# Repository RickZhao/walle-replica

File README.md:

# Wall-E Robot Replica
Robot and controller code for a Wall-E replica robot. For more information about the robot, visit https://wired.chillibasket.com/3d-printed-archive/arduino-pi/wall-e/

<br />

> **This fork adds two extra firmwares and custom hardware on top of the upstream project:**
>
> | Path | Framework | Description |
> |------|-----------|-------------|
> | `wall-e_xiaozhi/` | ESP-IDF | **Mainline**: single ESP32-S3 voice robot based on xiaozhi-esp32 (wake word + cloud LLM + MCP motion tools + web control panel + ML307R-DL 4G fallback (mini core board, GPIO2/3); eye display lives on the CAM module, disabled on the main MCU). See `docs/XIAOZHI_MIGRATION.md` |
> | `wall-e_esp32_cam/` | Arduino (ESP32-S3-CAM) | MJPEG camera streamer for a second ESP32-S3-CAM board |
> | `hardware/walle-shield/` | KiCad 10 | Modular backplane PCB replacing dupont wiring |
> | `hardware/` | — | New-hardware PCB design inputs: `另一套硬件方案.md` (third-party kit BOM), `新硬件BOM与尺寸.md` (BOM/sizes), `主板设计说明.md` (connectors/power/layout), `主板布局示意图.html` (layout incl. camera backplane & panel board) |
>
> The original Arduino UNO (`archive/arduino-pi/wall-e/`) + Raspberry Pi (`archive/arduino-pi/web_interface/`) setup below is still fully maintained. Chinese docs live in `docs/` (serial protocol, wiring, hardware list, migration notes).

<br />
<br />

## 1. Arduino Code (wall-e)
Main program to control the motors and servos of the robot. Features include:
1. An animation queue, keeping track of the next servo movements the robot needs to perform.
1. A random movement generator, allowing the robot to autonomously move and appear animated.
1. Velocity control of all servo motors, facilitating smooth accelerations and decelerations. 
1. Non-blocking serial parsing, allowing the movements of the robot to be remote controlled.
1. Battery level monitoring using a potential divider circuit.
<br />

## 2. Raspberry Pi Web Server (web_interface)
The web interface is programmed in Python and uses *Flask* to generate a server. The Raspberry Pi is connected via USB to the Arduino micro-controller. The main features are:
1. A JavaScript joystick, with which the movement of the robot can easily be controller.
1. Manual control of all the servo motors.
1. A list of movement animations which can be performed by the robot.
1. A list of sounds which can be played.
1. Settings page, where motor parameters, sound volume, and video options can be modified.
1. Gamepad support; on any modern browsers, you can use a connected Xbox of PlayStation controller to control the robot.
1. A simple login page to prevent everyone from having access to the controls (note: this is not a full access control system, please don't use this web interface on untrusted/public networks)
1. **[New]** Support for text-to-speech
1. **[New]** Program robot actions using CodeBlocks drag and drop editor within the browser.

*Image of the web interface and robot*

<br />
<br />

## Setup Instructions

### 1. Arduino

#### [a] Basic Installation
1. Ensure that the wiring of the electronics matches the diagram shown below.
1. Download/clone the folder "wall-e" from the GitHub repository.
1. Open `wall-e.ino` in the Arduino IDE; the files `animations.ino`, `MotorController.hpp` and `Queue.hpp` should automatically open on separate tabs of the IDE as well.
1. Install the `Adafruit_PWMServoDriver.h` library
	1. Go to Sketch -> Include Library -> Manage Libraries...
	1. Search for *Adafruit Servo*.
	1. Install latest version of the library.
1. Connect to the computer to the micro-controller with a USB cable. Ensure that the correct *Board* and *Port* are selected in the *Tools* menu.
1. Upload the sketch to the micro-controller.

*Diagram showing the wiring of the robot's electronic components*
<br />

> **New: Modular Backplane PCB** — A complete KiCad 10 backplane design is available in `hardware/walle-shield/`. It replaces the mess of dupont wires with a single 140×100 mm 2-layer board: solder the pin sockets/terminals/switch/fuse/resistors, then plug in the Arduino, TB6612FNG module, PCA9685 module and buck converter. Gerbers, drill files and BOM are already exported. See `hardware/walle-shield/README.md` for details.

> **New: New-hardware PCB design inputs (Plan A)** — Complete design inputs for the custom Plan-A double-sided stacked mainboard + camera backplane + front-panel board are ready in `hardware/`: `新硬件BOM与尺寸.md` (BOM & measured module sizes), `主板设计说明.md` (pin-by-pin connector definitions / power tree / layout), `主板布局示意图.html` (to-scale layout incl. mainboard top/bottom, camera backplane and panel board); referencing the third-party kit (`另一套硬件方案.md` + `另一套硬件-{主板,副板,摄像头背板}.png`).
<br />

<br />

#### [b] Testing the Main Program
1. Once the sketch has been uploaded to the Arduino, power on the 12V battery while the micro-controller is still connected to the computer.
1. Open the *Serial Monitor* (button in top-right of Arduino IDE). Set the baud rate to 115200.
1. To control the movement of the robot, send the characters 'w', 'a', 's' or 'd' to move forward, left, back or right respectively. Send 'q' to stop all movement.
1. To move the head, send the characters 'j', 'l', 'i' or 'k' to tilt the head left or right and the eyes upwards or downwards. At this stage, the servos may try to move further than they should and may look uncoordinated. This will be solved by performing the servo motor calibration steps below.

<br />

#### [c] Servo Motor Calibration
1. Download/clone the folder "wall-e_calibration" from the GitHub repository
1. Open `wall-e_calibration.ino` in the Arduino IDE.
1. Upload the sketch to the micro-controller, and open the serial monitor and set the baud rate to 115200.
1. The sketch is used to calibrate the maximum and minimum PWM pulse lengths required to move each servo motor across its desired range of motion. The standard LOW and HIGH positions of each of the servos can be seen on diagrams [on my website](https://wired.chillibasket.com/3d-printed-archive/arduino-pi/wall-e/). 
1. When starting the sketch and opening the serial monitor, a message should appear after 2-3 seconds, saying that it is ready to calibrate the LOW position of the first servo motor (the head rotation).
1. Send the character 'a' and 'd' to move the motor backwards and forwards by -10 and +10. For finer control, use the characters 'z' and 'c' to move the motor by -1 and +1. 
1. Once the motor is in the correct position, send the character 'n' to proceed to the calibration step. It will move on to the HIGH position of the same servo, after which the process will repeat for each of the 7 servos in the robot.
1. When all joints are calibrated, the sketch will output an array containing the calibration values to the serial monitor.
1. Copy the array, and paste it into [lines 144](https://github.com/chillibasket/walle-replica/blob/master/archive/arduino-pi/wall-e/wall-e.ino#L144) to 150 of the program *wall-e.ino*. The array should look similar to this:
    ```cpp
    int preset[][2] =  {{410,120},  // head rotation
                        {532,178},  // neck top
                        {120,310},  // neck bottom
                        {465,271},  // eye right
                        {278,479},  // eye left
                        {340,135},  // arm left
                        {150,360}}; // arm right
    ```

<br />

#### [d] Battery Level Detection (Optional)
When using batteries to power the robot, it is important to keep track of how much power is left. Some batteries may break if they are over-discharged, and the SD card of the Raspberry Pi may become corrupted if not enough power is delivered.
1. To use the battery level detection feature on the Arduino, connect the following resistors and wiring as shown in the image below. The resistors (potential divider) reduce the 12V voltage down to a value below 5V, which is safe for the Arduino to measure using its analogue pins. The recommended resistor values are `R1 = 100kΩ` and `R2 = 47kΩ`.
1. Uncomment [line 54](https://github.com/chillibasket/walle-replica/blob/master/archive/arduino-pi/wall-e/wall-e.ino#L54) `#define BAT_L` in the main Arduino sketch *wall-e.ino*.
1. If you are using different resistor values, change the value of the potential divider gain factor on line 54 of the sketch, according to the formula: `POT_DIV = R2 / (R1 + R2)`. 
1. The program should now automatically check the battery level every 10 seconds, and this level will be shown on the Raspberry Pi web-interface in the "Status" section.

<br />
*Diagram showing the wiring of the battery level detection circuit*

<br />

#### [e] oLed Display (Optional) (Contributed by: [hpkevertje](https://github.com/hpkevertje))
It is possible to integrate a small oLED display which will show the battery level of the robot on the front battery indicator panel. This feature requires the battery level detection circuit in the previous section to be enabled, and the screen will update every time the battery level is calculated. This function uses the u8g2 display library in page mode; on the Arduino UNO you may get a warning that the memory usage is high, but this warning can be ignored. 
1. To use the oLed display feature on the Arduino, connect an i2c oLed display to the i2c bus on the servo motor module (see diagram).
1. Install the U8g2 library in the Arduino library manager:
    1. Go to Sketch -> Include Library -> Manage Libraries...
    1. Search for *U8gt*. The library publisher is "oliver".
    1. Install the latest version of the library.
1. Uncomment [line 74](https://github.com/chillibasket/walle-replica/blob/master/archive/arduino-pi/wall-e/wall-e.ino#L74) `#define OLED` in the main Arduino sketch *wall-e.ino*.
1. If you are using a different display that is supported by the library, you can change the constructor on [line 78](https://github.com/chillibasket/walle-replica/blob/master/archive/arduino-pi/wall-e/wall-e.ino#L78) as documented on the [library reference page](https://github.com/olikraus/u8g2/wiki/u8g2setupcpp#constructor-reference). The default is for an SH1106_128X64_NONAME display.

<br />
*Diagram showing the wiring of the oLed display*

<br />

#### [f] Adding your own Servo Animations (Optional)
My code comes with two animations which replicate scenes from the movie; the eye movement Wall-E does when booting-up, and a sequence of motions as Wall-E inquisitively looks around. From version 2.7 of the code, I've now made it easier to add your own servo motor animations so that you can make your Wall-E do other movements...
1. Open up the file `animations.ino`, which is located in the same folder as the main Arduino sketch. 
1. Each animation command consists of the positions you want all the servo motors to move to, and the amount of time the animation should wait until moving on to the next instruction.
1. You can add a new animation by inserting an extra `case` section into the switch statement. You should slot your extra code into the space above the `default` section. For example:
    ```cpp
    case 3:
            // --- Title of your new motion sequence ---
            //          time,head,necT,necB,eyeR,eyeL,armL,armR
            queue.push({  12,  48,  40,   0,  35,  45,  60,  59});
            queue.push({1500,  48,  40,  20, 100,   0,  80,  80});
            // Add as many additional movements here as you need to complete the animation
            // queue.push({time, head rotation, neck top, neck bottom, eye right, eye left, arm left, arm right})
            break;
    ```
1. The time needs to be a number in milliseconds (for example, 3.5 seconds = 3500)
1. The servo motor position commands need to be an integer number between 0 to 100, where `0 = LOW` and `100 = HIGH` servo position as calibrated in the `wall-e_calibration.ino` sketch.
1. If you want to disable a motor for a specific move, you can use -1. 

<br />
<br />

### 2. Raspberry Pi Web Server

#### [a] Hardware Setup
1. Connect the power cable of the Raspberry Pi to the USB power output port on the 12V to 5V buck converter.
2. Connect the USB data cable from the Arduino to the Raspberry Pi.
3. If you have a Raspberry Pi camera, plug the ribbon cable into the CSI camera connector.
4. For setup and installation, you can plug in a monitor into the HDMI port and a USB keyboard and mouse. Alternatively you can connect to and configure the Raspberry Pi from a different computer [using SSH](https://www.raspberrypi.com/documentation/computers/remote-access.html#ssh).
 
<br />

#### [b] Basic Installation
1. Setup the Raspberry Pi to run the latest version of Raspberry Pi OS Desktop. The setup instructions can be found on the [Raspberry Pi website](https://www.raspberrypi.com/documentation/computers/getting-started.html). Make sure that the Raspberry Pi is connected to the internet. 
2. Open the "Terminal" command line on the Raspberry Pi.
3. Clone repository into the home directory of the Raspberry Pi:
```shell
cd ~
git clone https://github.com/chillibasket/walle-replica.git
```

<br />

> [!NOTE]
> You can configure the web-interface settings by editing the "config.py" file:
> * Open the config file: `nano ~/walle-replica/archive/arduino-pi/web_interface/config.py`
> * On line [14](https://github.com/chillibasket/walle-replica/blob/master/archive/arduino-pi/web_interface/config.py#L14) you can change the password for the web interface. The default password is "walle"
> * On line [15](https://github.com/chillibasket/walle-replica/blob/master/archive/arduino-pi/web_interface/config.py#L15) the default serial port which is used to connect to the Arduino can be set. You can find a list of all the connected serial ports using the `dmseg | grep tty` command.
> * On lines [16](https://github.com/chillibasket/walle-replica/blob/master/archive/arduino-pi/web_interface/config.py#L16) and [17](https://github.com/chillibasket/walle-replica/blob/master/archive/arduino-pi/web_interface/config.py#L17) you can configure whether the Arduino and camera should automatically connect when starting up the web server.

<br />

4. Once you have finished editing the configurations, run the installation script which sets up all the required libraries for you (note - this may take some time to complete):
```shell
cd ~/walle-replica
sudo chmod +x ./archive/arduino-pi/raspi-setup.sh
sudo ./archive/arduino-pi/raspi-setup.sh
```

<br />

#### [c] Using the Web Server
1. If the installation completed successfully, the webserver should start automatically when the Raspberry Pi is powered on. This is done using a [Systemd service](https://learn.sparkfun.com/tutorials/how-to-run-a-raspberry-pi-program-on-startup/all#method-3-systemd). 
1. On the Raspberry Pi you can view the web interface from the browser at http://localhost:5000
1. To view the interface from a different computer on the same WiFi network, you first need to determine the current IP address of the Raspberry Pi on your network using the command: `hostname -I`
1. To access the web interface, open a browser on any computer/device on the same network and type in the IP address of the Raspberry Pi, follow by `:5000`. For example `192.168.1.10:5000`
1. To start controlling the robot, you first need to make sure that the serial communication with the Arduino has started. To do this, go to the `Settings` tab of the web-interface, select the correct serial port from the drop-down list and press on the `Reconnect` button. If the configurations were set up correctly, this should happen automatically.

<br />

> [!TIP]
> Here are some useful commands to control the web interface:
> * To stop the automatic web interface service: `sudo systemd stop walle.service`
> * To disable start on boot: `sudo systemd disable walle.service`
> * To reenable start on boot: `sudo systemd enable walle.service`
> * To start the service after it has been stopped: `sudo systemd start walle.service`
> * View the status of the service and check for errors: `sudo systemd status walle.service`
> * If you want to manually run the web server from the terminal, for example to check for errors: `python3 ~/walle-replica/archive/arduino-pi/web_interface/app.py`. You can then press `CTRL + C` to stop the web server again.

<br />

#### [d] Controlling the Robot using Blocky (Contributed by: [dkrey](https://github.com/dkrey))
Since version 3.0, a new tab has been added to the web interface where the robot can be controlled using a drag-and-drop scripting language. Simply drag the actions you want to perform from the left sidebar and drop them into the editor area. For example you can drive Wall-E, move the actuators, and play audio sounds. This is a great way for kids to learn the basics of programming while having fun!

For the commands which drive the motors, you may need to tune the parameters at the bottom of the "config.py" file on lines [25](https://github.com/chillibasket/walle-replica/blob/master/archive/arduino-pi/web_interface/config.py#L25) to [28](https://github.com/chillibasket/walle-replica/blob/master/archive/arduino-pi/web_interface/config.py#L28) to make sure that the speed and turning amount is correct. 

<br />

#### [e] Adding a Camera Stream (Optional)

The web server automatically supports any camera which connects to the CSI connector on the Raspberry Pi with a ribbon cable. Unfortunately USB web cameras are not supported by this system, but I hope to add support for them again in the future. 

<br />

#### [f] Adding new Sounds (Optional)
1. By default the Raspberry should automatically select whether to output audio to the HDMI port or the headphone jack. However, you can ensure that it always uses the headphone jack with the following command: `amixer cset numid=3 1`
1. Make sure that all the sound files you want to use are of type `*.wav`. Most music/sound editors should be able to convert the sound file to this format.
1. Change the file name so that it has the following format: `[group name]_[file name]_[length in milliseconds].wav`. For example: `voice_eva_1200.wav`. In the web-interface, the audio files will be grouped using the "group name" and sorted alphabetically.
1. Upload the sound file to Raspberry Pi in the following folder: `~/walle-replica/archive/arduino-pi/web_interface/static/sounds/`
1. All the files should appear in the web interface when you reload the page. If the files do not appear, you may need to change the privileges required to access the folder: `sudo chmod -R 755 ~/walle-replica/archive/arduino-pi/web_interface/static/sounds`

<br />

#### [g] Set up the Raspberry Pi as a WiFi hotspot *(Optional)*
If you would like to control the robot outdoors or at conventions, there may not be any safe WiFi networks you can connect to. To overcome this issue the Raspberry Pi can broadcast its own WiFi network. You can then connect the computer/phone/tablet you are using to control the robot directly to this network.

To set up the WiFi hotspot, we will use the [RaspAP project](https://raspap.com/) which takes care of all the configuration and tools to get the system working. The following instructions are based on their quick installation guide:

1. Update Raspian, the kernel and firmware (and then reboot):
    ```
    sudo apt-get update
    sudo apt-get dist-upgrade
    sudo reboot now
    ```
1. Ensure that you have set the correct WiFi country in raspi-config’s Localisation Options: `sudo raspi-config`
1. Run the quick installer: `curl -sL https://install.raspap.com | bash`
    1. For the first few yes/no prompts which will appear during the install, type “y” (yes) to accept all of the recommended settings. The final two prompts (Ad Blocking and the next one) are not required so you can type “n” (no) for those.
1. Reboot the Raspberry Pi again to implement the changes: `sudo reboot`
1. Now the Raspberry Pi should be broadcasting a WiFi network with the following details:
    1. SSID (wifi name): `raspi-webgui`
    1. Password: `ChangeMe`
1. After connecting to the WiFi network from a your computer, phone or tablet, the Wall-E web-interface can be opened by typing this address into your browser: `http://10.3.141.1:5000`
1. (Recommended) To change the WiFi name and password, go to the WiFi configuration webpage at: `http://10.3.141.1`. The default username is `admin` and password is `secret`.
    1. Click on “Hotspot” in the left sidebar. In the “Basic” tab you can change the WiFi network name, while the WiFi password can be changed in the “Security” tab.
    1. To change the admin password for the interface used to manage the WiFi settings, click on the “Admin” icon in the top-right of the interface.

<br />
<br />

## Changelog

#### 9th June 2024 (Version 3.0)
1. Major revision of the Python code to implement best practices and make it more robust.
1. Added text to speech and integrated blocky scripting into the web interface (thanks to [dkrey](https://github.com/dkrey) for contributing this).
1. Switched the camera streamer to PiCamera2 since the old streamer no longer worked. 
1. Implemented an installation script to make setup a lot faster and easier. 

#### 31st October 2021 (Version 2.92)
1. Added options in *app.py* to automatically connect to the Arduino and to start the camera stream when the web-interface is opened for the first time.

#### 30th October 2021 (Version 2.91)
1. Changed camera stream port from 8081 to 8080 inline with changes made to the start/stop script.
1. Improved the camera setup instructions, listing all steps explicitly rather than linking to an external repository.

#### 29th May 2021 (Version 2.9)
1. Improved code commenting and variable/parameter naming to make it easier to understand.
1. Fixed bugs related to motor deadzone and trim parameters.

#### 21st March 2021 (Version 2.8)
1. Updated instructions of how to use an oLed display. 

#### 19th December 2020
1. Updated instructions of how to set up a WiFi hotspot on the Raspberry Pi. 
1. Added offline Lato font files to prevent errors when running the web-interface while disconnected from the internet.

#### 7th August 2020 (Version 2.7)
1. Added a soft servo start function to the main Wall-E sketch and the servo calibration sketch. This prevents the servos from jumping as violently on startup.
1. Changed the data-type of the animation queue to reduce the amount of dynamic memory required. Also updated the Queue class so that the buffer memory can be declared globally; this means the compiler can keep track of how much memory the queue actually uses.
1. Moved the preset servo animations into a separate file, to make it easier to add your own animations. 

#### 20th June 2020
1. Minor bug fixes of the `Queue.hpp` and `MotoController.hpp` classes.
1. Updated commenting of code to make it more consistent.

#### 16th February 2020
1. Added gamepad support; any controller can now be used (such as the Xbox or PlayStation controllers) to puppet the robot.
1. Improved serial port handling; in the settings tab, all of the available serial ports are listed in a drop-down menu. 
1. New status indicators are now shown below the video stream. They visualise whether the Arduino and/or gamepad are connected.
1. Added support for battery level detection in both the Arduino code and the Raspberry Pi web interface.
1. Fixed the bug where the virtual joystick no longer worked properly when the window was resized.
1. Plus many other bug fixes!

#### 25th January 2020
1. Restructured the web-interface to make it display more nicely on mobile devices; fancy icons are now used!
1. Added manual servo control - this allows individual servos to be controlled directly from the web-interface.
1. Improved error handling - error messages are now consistently displayed in a pop-up at the bottom of the page.
1. Added instructions about how to automatically start server on boot to the Readme.

#### 31st October 2019
1. Fixed some bugs related to sound playback.
1. Added 2 sample sound files, which ensures that the sound directory is included in the git files.

#### 30th October 2019 
1. Added *wall-e_calibration.ino*, with which the maximum and minimum pulse widths of the servo motors can be calibrated.
1. Updated *wall-e.ino* to use relative coordinates rather than absolute servo pulse widths for the animation presets. This allows the servo calibration data to be used to ensure the movements are the same on all variants of the robot.

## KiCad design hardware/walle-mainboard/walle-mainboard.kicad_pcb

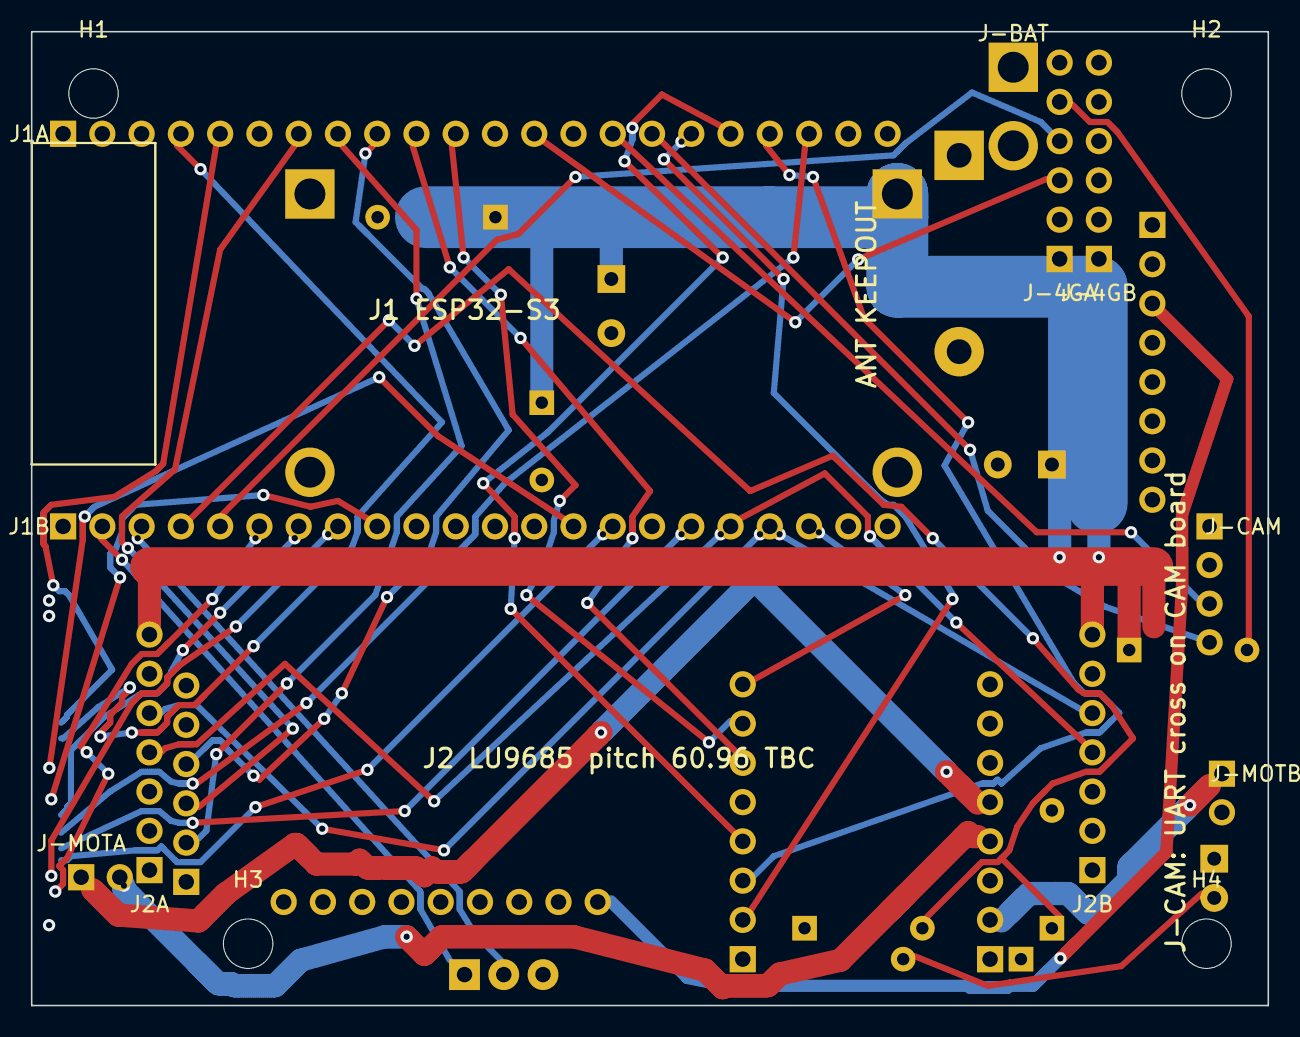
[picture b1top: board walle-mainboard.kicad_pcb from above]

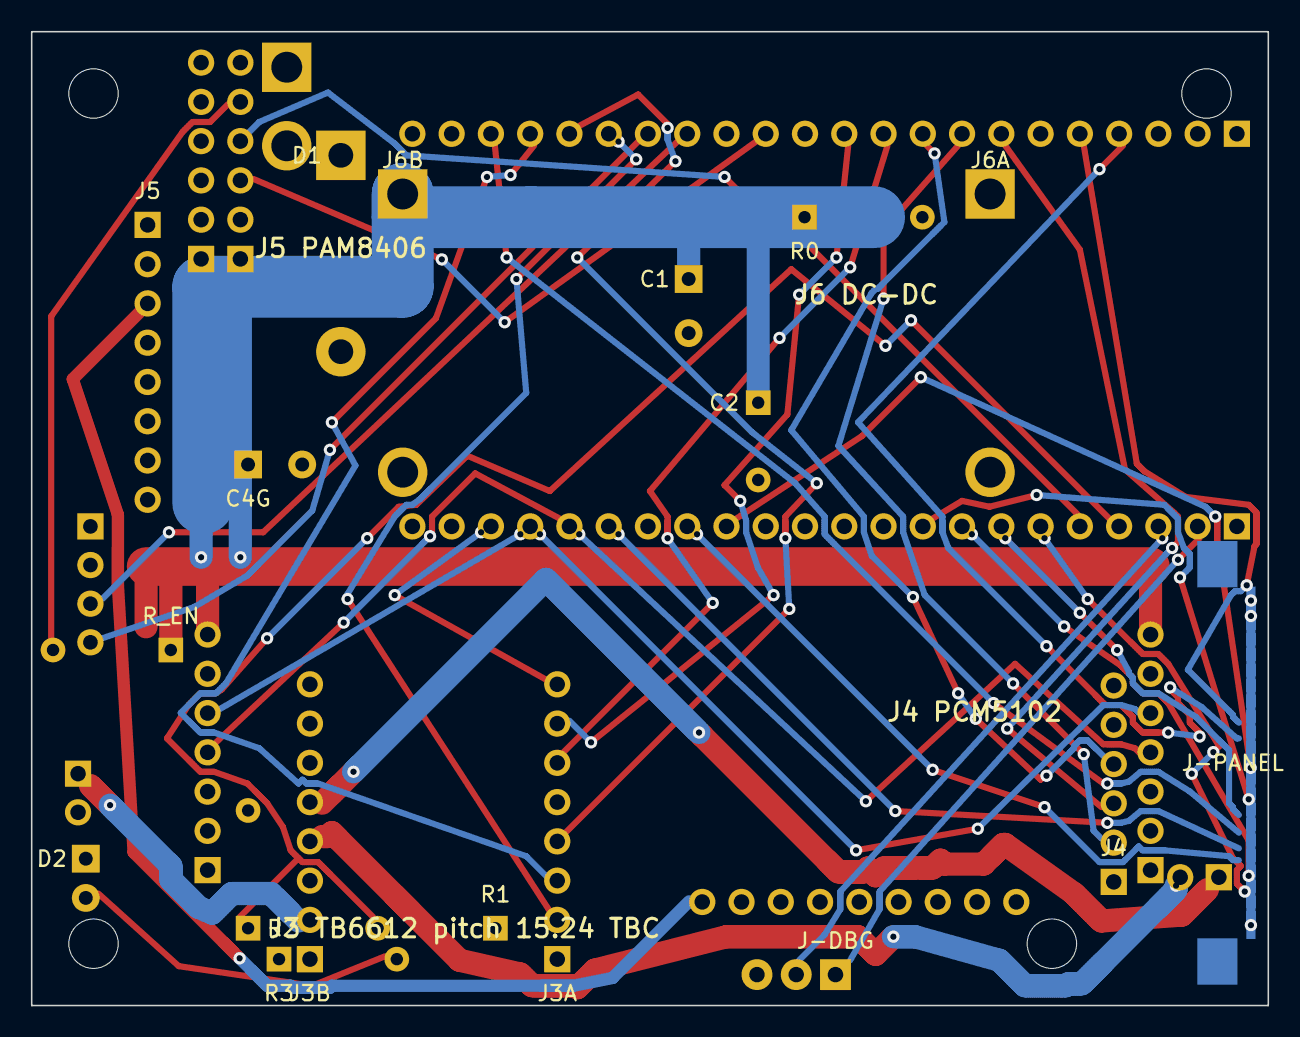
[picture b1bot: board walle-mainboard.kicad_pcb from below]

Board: 4 copper layers, 80.0 x 63.0 mm, 32 parts (18 on the bottom side), 48 nets.

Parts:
C1, C4G: 470uF; cp8
C2: 100nF; cdisc5
D1: P600; p600
D2: LED; led3
H1, H2, H3, H4: MountingHole_3.2mm_M3
J1A: ESP32-S3 L; sock22
J1B: ESP32-S3 R; sock22
J2A: LU9685 A; sock7
J2B: LU9685 B; sock7
J3A: TB6612 L; sock8
J3B: TB6612 R; sock8
J4: PCM5102; pcm5102
J5: PAM8406; hdr8
J6A: DCDC IN; j6
J6B: DCDC OUT; j6
J-4GA: ML307R L; sock6
J-4GB: ML307R R; sock6
J-BAT: 12V IN; jbat
J-CAM: CAM XHB4; xh4
J-DBG: DBG; jdbg
J-MOTA: MOT-A XH2; xh2
J-MOTB: MOT-B XH2; xh2
J-PANEL: FFC22; ffc22
R0: 0R; rax
R1: 100k; rax
R2: 20k; rax
R3: 1k; rax
R_EN: 100k; rax

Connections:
4G_EN: J-4GA.5, R_EN.2
4G_RX: J1A.13, J-4GA.3
4G_TX: J1B.5, J-4GA.4
+3V3: J1A.1, J4.11, J-PANEL.2, J-PANEL.22
+5V: J1A.21, J2A.6, J2B.6, J3A.5, J3B.7, J4.6, J5.1, J-CAM.1, J-PANEL.1, R0.2, R3.1
+5V_SERVO: C1.1, C2.1, C4G.1, J2A.7, J2B.7, J6B.1, J-4GA.1, J-4GB.1, R0.1, R_EN.1
+12V: D1.1, J3B.8, J6A.1
+12V_RAW: D1.2, J-BAT.1, R1.1
BAT_ADC: J1B.4, R1.2, R2.1
BTN_BOOT: J1B.14, J-PANEL.12
BTN_RST: J1B.7, J-PANEL.15
BTN_VDN: J1B.9, J-PANEL.14
BTN_VUP: J1B.10, J-PANEL.13
CAM_RX: J1A.16, J-CAM.4
CAM_TX: J1A.15, J-CAM.3
DAC_BCK: J1A.8, J4.2
DAC_DIN: J1A.7, J4.3
DAC_L: J4.15, J5.3
DAC_LCK: J1A.9, J4.4
DAC_R: J4.13, J5.4
GND: C1.2, C2.2, C4G.2, D2.1, J1A.22, J1B.1, J2A.1, J2B.1, J3A.1, J3B.1, J3B.6, J4.5, J4.12, J4.14, J5.2, J6A.2, J6B.2, J-4GA.2, J-4GB.2, J-BAT.2, J-CAM.2, J-DBG.3, J-PANEL.3, J-PANEL.4, J-PANEL.21, R2.2
I2C_SCL: J1B.18, J2A.4, J2B.4
I2C_SDA: J1B.19, J2A.5, J2B.5
MIC_SCK: J1A.5, J-PANEL.9
MIC_SD: J1A.6, J-PANEL.11
MIC_WS: J1A.4, J-PANEL.10
MOTA_1: J3B.5, J-MOTA.1
MOTA_2: J3B.4, J-MOTA.2
MOTB_1: J3B.2, J-MOTB.1
MOTB_2: J3B.3, J-MOTB.2
MOT_AIN1: J1A.10, J3A.6
MOT_AIN2: J1A.11, J3A.7
MOT_BIN1: J1A.18, J3A.4
MOT_BIN2: J1A.19, J3A.3
MOT_PWMA: J1B.20, J3A.8
MOT_PWMB: J1A.17, J3A.2
unnamed: D2.2, R3.2
SPK_L+: J5.5, J-PANEL.5
SPK_L-: J5.6, J-PANEL.6
SPK_R+: J5.7, J-PANEL.7
SPK_R-: J5.8, J-PANEL.8
TFT_BLK: J1B.6, J-PANEL.20
TFT_DC: J1B.8, J-PANEL.19
TFT_RES: J1B.15, J-PANEL.18
TFT_SCL: J1A.20, J-PANEL.16
TFT_SDA: J1B.17, J-PANEL.17
UART0_RX: J1B.3, J-DBG.2
UART0_TX: J1B.2, J-DBG.1

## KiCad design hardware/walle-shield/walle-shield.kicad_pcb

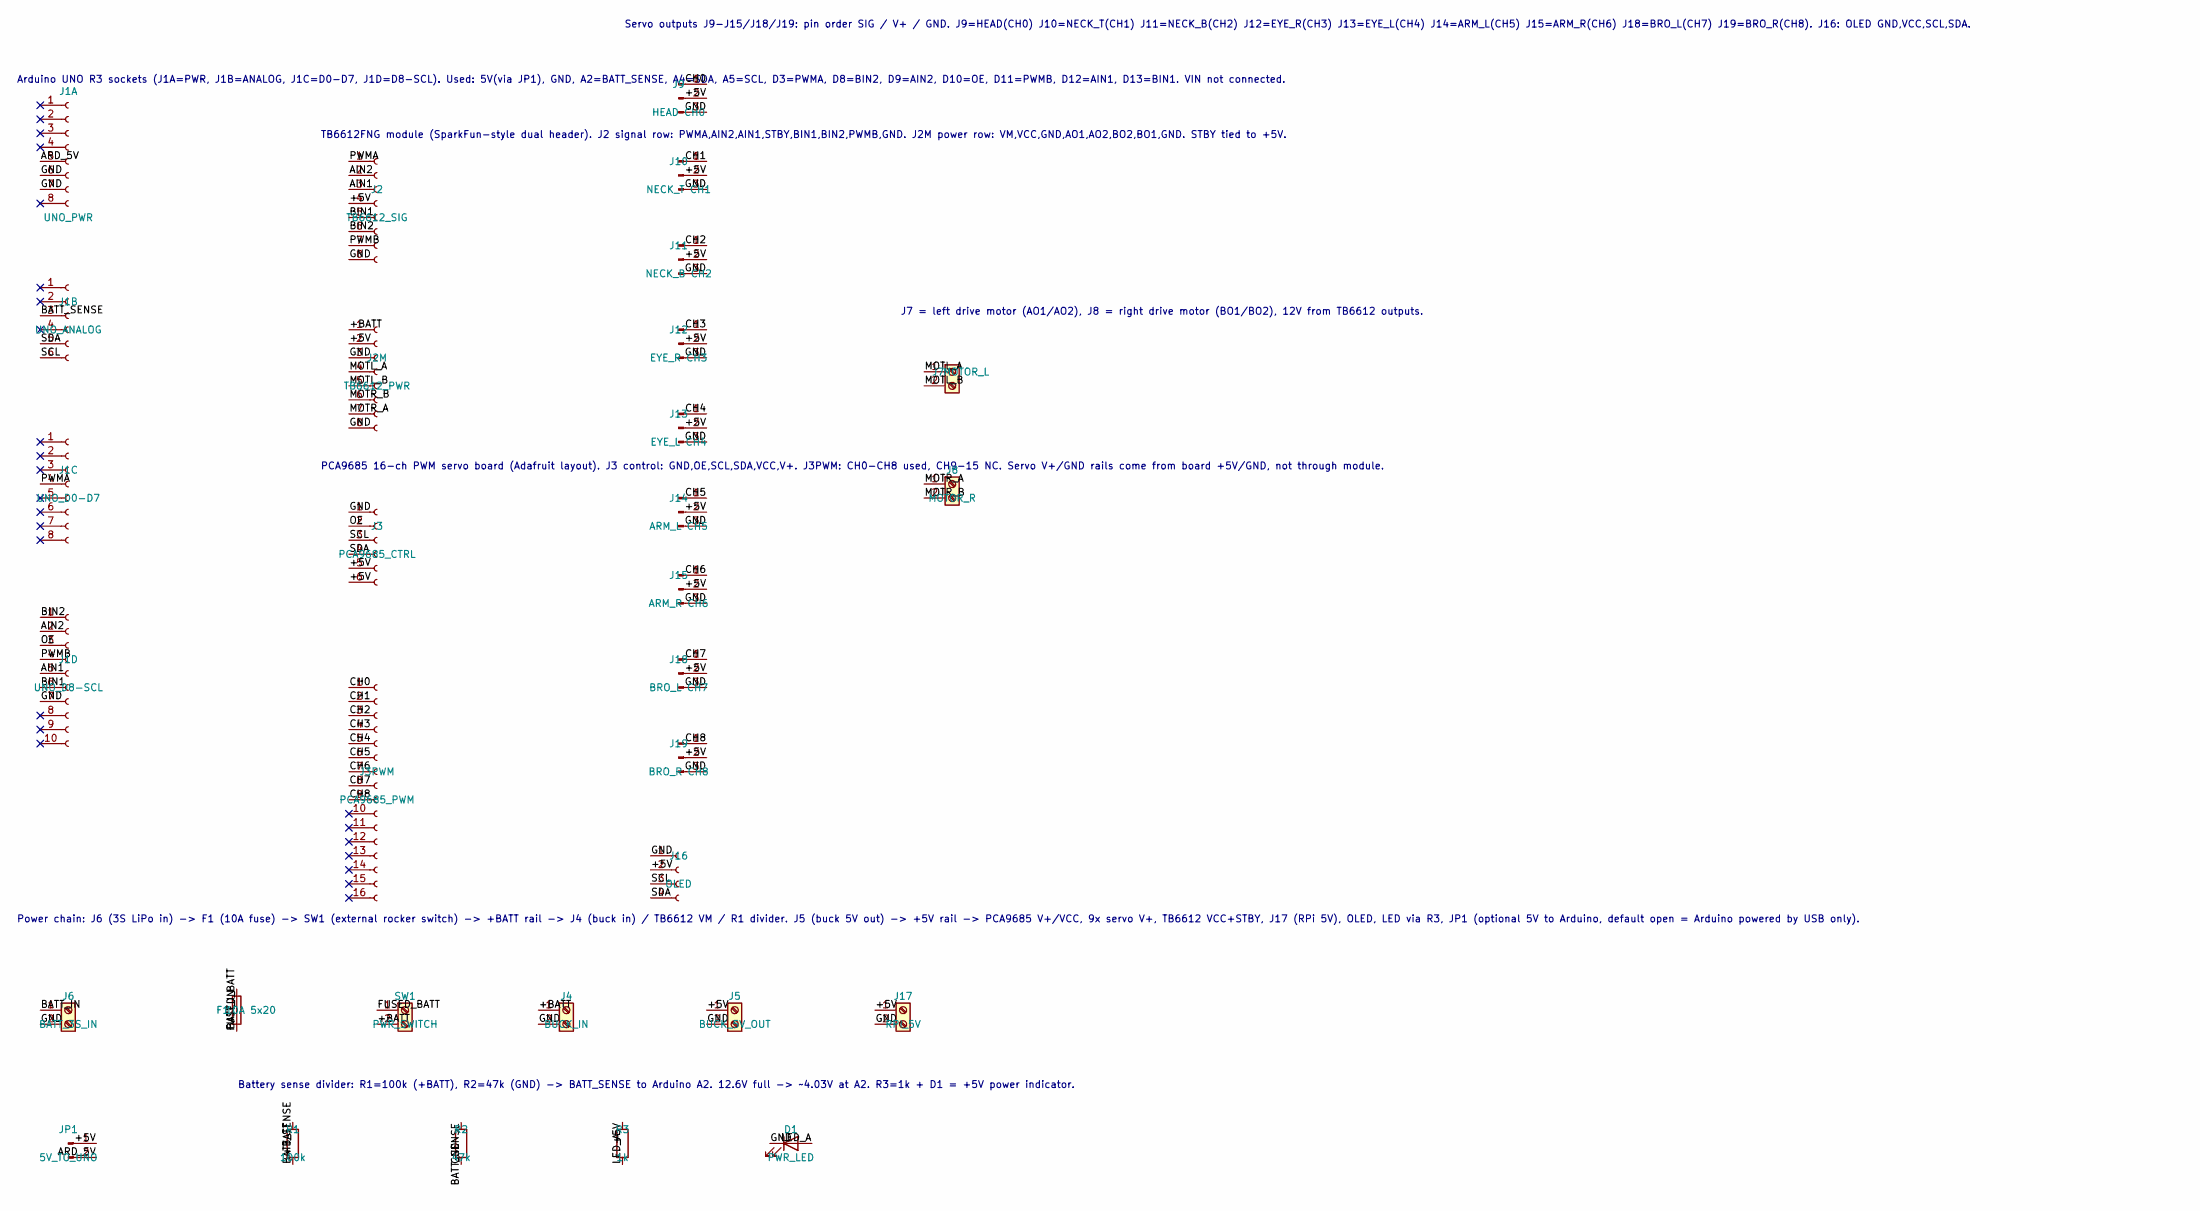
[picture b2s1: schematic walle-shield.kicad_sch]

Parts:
D1: PWR_LED; LED_D5.0mm
F1: 10A 5x20; Fuseholder_Clip-5x20mm_Keystone_3512_Inline_P23.62x7.27mm_D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
J1A: UNO_PWR; PinSocket_1x08_P2.54mm_Vertical
J1B: UNO_ANALOG; PinSocket_1x06_P2.54mm_Vertical
J1C: UNO_D0-D7; PinSocket_1x08_P2.54mm_Vertical
J1D: UNO_D8-SCL; PinSocket_1x10_P2.54mm_Vertical
J2: TB6612_SIG; PinSocket_1x08_P2.54mm_Vertical
J2M: TB6612_PWR; PinSocket_1x08_P2.54mm_Vertical
J3: PCA9685_CTRL; PinSocket_1x06_P2.54mm_Vertical
J3PWM: PCA9685_PWM; PinSocket_1x16_P2.54mm_Vertical
J4: BUCK_IN; TerminalBlock_Phoenix_MKDS-1,5-2-5.08_1x02_P5.08mm_Horizont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
J5: BUCK_5V_OUT; TerminalBlock_Phoenix_MKDS-1,5-2-5.08_1x02_P5.08mm_Horizont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
J6: BATT_3S_IN; TerminalBlock_Phoenix_MKDS-1,5-2-5.08_1x02_P5.08mm_Horizont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
J7: MOTOR_L; TerminalBlock_Phoenix_MKDS-1,5-2-5.08_1x02_P5.08mm_Horizont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
J8: MOTOR_R; TerminalBlock_Phoenix_MKDS-1,5-2-5.08_1x02_P5.08mm_Horizont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
J9: HEAD CH0; PinHeader_1x03_P2.54mm_Vertical
J10: NECK_T CH1; PinHeader_1x03_P2.54mm_Vertical
J11: NECK_B CH2; PinHeader_1x03_P2.54mm_Vertical
J12: EYE_R CH3; PinHeader_1x03_P2.54mm_Vertical
J13: EYE_L CH4; PinHeader_1x03_P2.54mm_Vertical
J14: ARM_L CH5; PinHeader_1x03_P2.54mm_Vertical
J15: ARM_R CH6; PinHeader_1x03_P2.54mm_Vertical
J16: OLED; PinSocket_1x04_P2.54mm_Vertical
J17: RPI_5V; TerminalBlock_Phoenix_MKDS-1,5-2-5.08_1x02_P5.08mm_Horizont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
J18: BRO_L CH7; PinHeader_1x03_P2.54mm_Vertical
J19: BRO_R CH8; PinHeader_1x03_P2.54mm_Vertical
JP1: 5V_TO_UNO; PinHeader_1x02_P2.54mm_Vertical
R1: 100k; R_Axial_DIN0207_L6.3mm_D2.5mm_P7.62mm_Horizontal
R2: 47k; R_Axial_DIN0207_L6.3mm_D2.5mm_P7.62mm_Horizontal
R3: 1k; R_Axial_DIN0207_L6.3mm_D2.5mm_P7.62mm_Horizontal
SW1: PWR_SWITCH; TerminalBlock_Phoenix_MKDS-1,5-2-5.08_1x02_P5.08mm_Horizont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

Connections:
+5V: J2.4, J2M.2, J3.5, J3.6, J5.1, J9.2, J10.2, J11.2, J12.2, J13.2, J14.2, J15.2, J16.2, J17.1, J18.2, J19.2, JP1.1, R3.1
+BATT: J2M.1, J4.1, R1.1, SW1.2
AIN1: J1D.5, J2.3
AIN2: J1D.2, J2.2
ARD_5V: J1A.5, JP1.2
BATT_IN: F1.1, J6.1
BATT_SENSE: J1B.3, R1.2, R2.1
BIN1: J1D.6, J2.5
BIN2: J1D.1, J2.6
CH0: J3PWM.1, J9.1
CH1: J3PWM.2, J10.1
CH2: J3PWM.3, J11.1
CH3: J3PWM.4, J12.1
CH4: J3PWM.5, J13.1
CH5: J3PWM.6, J14.1
CH6: J3PWM.7, J15.1
CH7: J3PWM.8, J18.1
CH8: J3PWM.9, J19.1
FUSED_BATT: F1.2, SW1.1
GND: D1.1 (K), J1A.6, J1A.7, J1D.7, J2.8, J2M.3, J2M.8, J3.1, J4.2, J5.2, J6.2, J9.3, J10.3, J11.3, J12.3, J13.3, J14.3, J15.3, J16.1, J17.2, J18.3, J19.3, R2.2
LED_A: D1.2 (A), R3.2
MOTL_A: J2M.4, J7.1
MOTL_B: J2M.5, J7.2
MOTR_A: J2M.7, J8.1
MOTR_B: J2M.6, J8.2
OE: J1D.3, J3.2
PWMA: J1C.4, J2.1
PWMB: J1D.4, J2.7
SCL: J1B.6, J3.3, J16.3
SDA: J1B.5, J3.4, J16.4

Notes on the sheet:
Arduino UNO R3 sockets (J1A=PWR, J1B=ANALOG, J1C=D0-D7, J1D=D8-SCL). Used: 5V(via JP1), GND, A2=BATT_SENSE, A4=SDA, A5=SCL, D3=PWMA, D8=BIN2, D9=AIN2, D10=OE, D11=PWMB, D12=AIN1, D13=BIN1. VIN not connected.
TB6612FNG module (SparkFun-style dual header). J2 signal row: PWMA,AIN2,AIN1,STBY,BIN1,BIN2,PWMB,GND. J2M power row: VM,VCC,GND,AO1,AO2,BO2,BO1,GND. STBY tied to +5V.
PCA9685 16-ch PWM servo board (Adafruit layout). J3 control: GND,OE,SCL,SDA,VCC,V+. J3PWM: CH0-CH8 used, CH9-15 NC. Servo V+/GND rails come from board +5V/GND, not through module.
Servo outputs J9-J15/J18/J19: pin order SIG / V+ / GND. J9=HEAD(CH0) J10=NECK_T(CH1) J11=NECK_B(CH2) J12=EYE_R(CH3) J13=EYE_L(CH4) J14=ARM_L(CH5) J15=ARM_R(CH6) J18=BRO_L(CH7) J19=BRO_R(CH8). J16: OLED GND,VCC,SCL,SDA.
Power chain: J6 (3S LiPo in) -> F1 (10A fuse) -> SW1 (external rocker switch) -> +BATT rail -> J4 (buck in) / TB6612 VM / R1 divider. J5 (buck 5V out) -> +5V rail -> PCA9685 V+/VCC, 9x servo V+, TB6612 VCC+STBY, J17 (RPi 5V), OLED, LED via R3, JP1 (optional 5V to Arduino, default open = Arduino pow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
J7 = left drive motor (AO1/AO2), J8 = right drive motor (BO1/BO2), 12V from TB6612 outputs.
Battery sense divider: R1=100k (+BATT), R2=47k (GND) -> BATT_SENSE to Arduino A2. 12.6V full -> ~4.03V at A2. R3=1k + D1 = +5V power indicator.

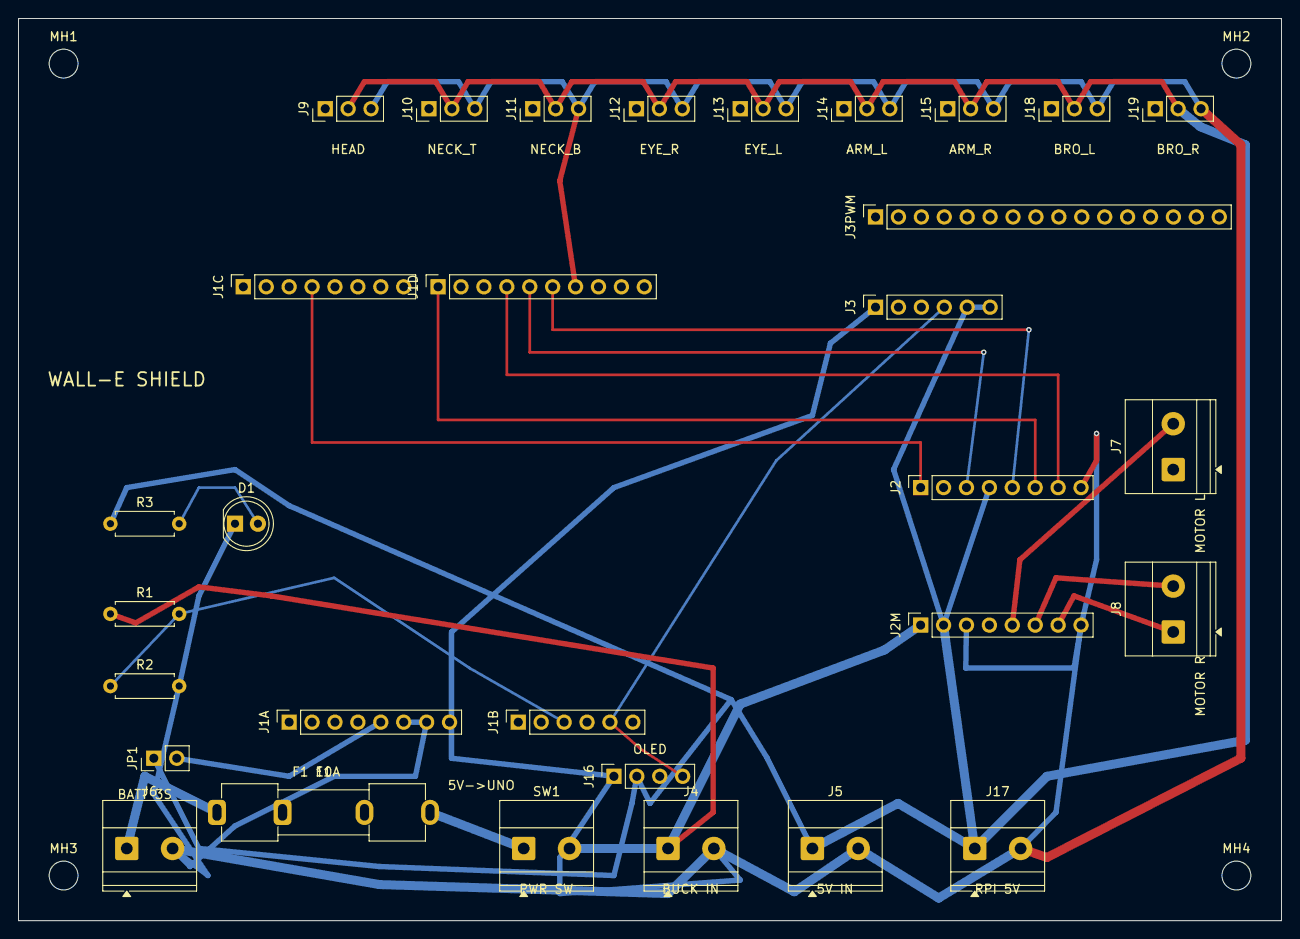
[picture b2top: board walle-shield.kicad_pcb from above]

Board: 2 copper layers, 140.0 x 100.0 mm, 35 parts (0 on the bottom side), 30 nets.

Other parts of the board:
MH1, MH2, MH3, MH4: MH_3.2mm_NPTH

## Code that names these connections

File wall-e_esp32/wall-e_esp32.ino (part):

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#define MOTOR_DRIVER_TB6612FNG       // Dual-direction-pin driver (TB6612FNG)
// #define MOTOR_DRIVER_ARDUINO_SHIELD // Original Arduino Motor Shield Rev2

#define DIRECTION_L_PIN  5           // Motor direction pins (TB6612: AIN1/BIN1)
#define DIRECTION_R_PIN  15
#define PWM_SPEED_L_PIN  4           // Motor PWM pins (TB6612: PWMA/PWMB)
#define PWM_SPEED_R_PIN  7
#define MOTOR_STBY_PIN   17          // TB6612 standby pin (driven HIGH)
#define SERVO_ENABLE_PIN 10          // Servo driver board output enable (OE) pin

#define I2C_SDA_PIN      8           // I2C pins for the servo driver board
#define I2C_SCL_PIN      9           // (and the optional oLED display)

#ifdef MOTOR_DRIVER_TB6612FNG
	#define DIRECTION_L_PIN2 6       // Second complementary direction pin (TB6612: AIN2/BIN2)
	#define DIRECTION_R_PIN2 16
#else
	#define BRAKE_L_PIN  6           // Motor brake pins (Arduino Motor Shield Rev2 only)
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	digitalWrite(SERVO_ENABLE_PIN, HIGH);

	// ESP32: route I2C to the chosen pins before initialising the PWM driver
	Wire.begin(I2C_SDA_PIN, I2C_SCL_PIN);

	// Communicate with servo driver board (Analog servos run at ~60Hz)
	pwm.begin();
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

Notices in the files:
wall-e_esp32/wall-e_esp32.ino:
@copyright  Copyright (C) 2021 - Distributed under MIT license
README.md:
GPLv3 License
